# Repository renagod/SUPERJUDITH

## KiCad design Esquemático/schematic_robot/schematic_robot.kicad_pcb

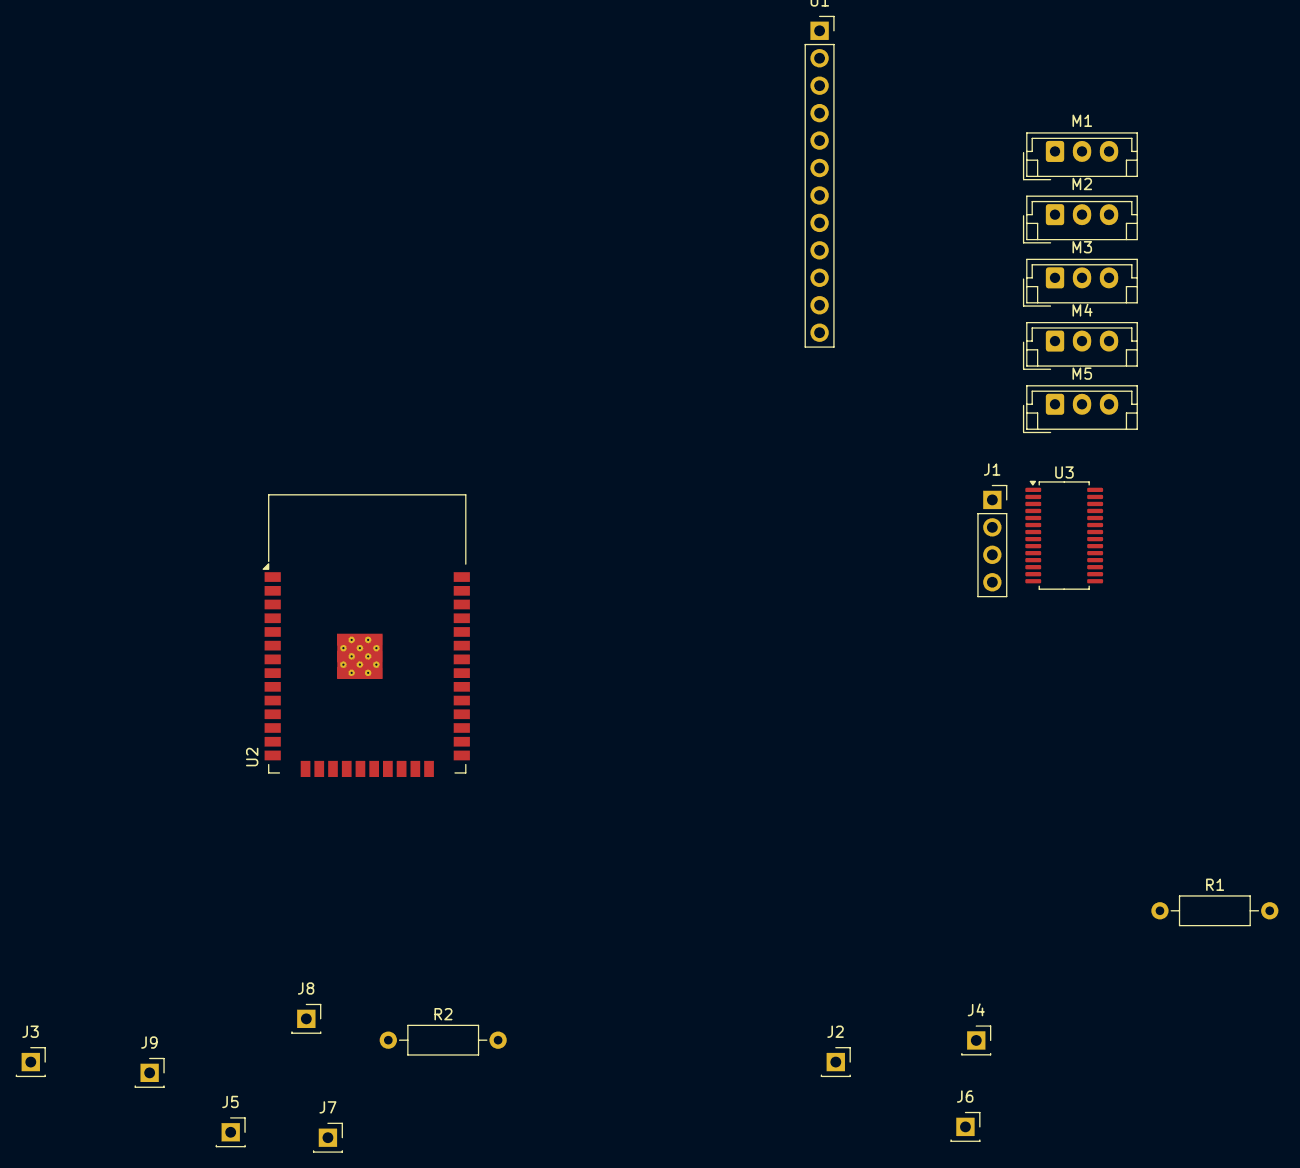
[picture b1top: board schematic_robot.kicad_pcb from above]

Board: 2 copper layers, 19 parts (0 on the bottom side), 18 nets, no tracks yet.

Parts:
J1: Conn_01x04_Pin; PinSocket_1x04_P2.54mm_Vertical
J2, J3, J4, J5, J6, J7, J8, J9: Conn_01x01_Socket; PinSocket_1x01_P2.54mm_Vertical
M1, M2, M3, M4, M5: Motor_Servo; JST_EH_B3B-EH-A_1x03_P2.50mm_Vertical
R1, R2: 4.7k; R_Axial_DIN0207_L6.3mm_D2.5mm_P10.16mm_Horizontal
U1: TB6600; PinSocket_1x12_P2.54mm_Vertical
U2: ESP32-WROOM-32
U3: PCA9685PW; TSSOP-28_4.4x9.7mm_P0.65mm

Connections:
5V: J3.1, J8.1, M1.2 (+), M2.2 (+), M3.2 (+), M4.2 (+), M5.2 (+), R1.1, R2.1, U2.2 (VDD), U3.14 (VSS)
12V: J2.1, J6.1, U1.12 (VCC)
DIR+: U1.4 (DIR+), U2.11 (IO26)
ENA+: U1.2 (ENA+), U2.13 (IO14)
Earth: J5.1, J7.1, U1.1 (ENA-), U1.3 (DIR-), U1.5 (PUL-), U1.11 (GND)
GND: J4.1, J9.1, M1.3 (-), M2.3 (-), M3.3 (-), M4.3 (-), M5.3 (-), U2.1 (GND), U2.15 (GND), U2.38 (GND), U2.39 (GND), U3.25 (EXTCLK), U3.28 (VDD)
unnamed: J1.1, U1.8 (B+)
unnamed: J1.2, U1.7 (B-)
unnamed: J1.3, U1.9 (A-)
unnamed: J1.4, U1.10 (A+)
PUL+: U1.6 (PUL+), U2.10 (IO25)
PWM1: M1.1 (PWM), U3.6 (LED0)
PWM2: M2.1 (PWM), U3.7 (LED1)
PWM3: M3.1 (PWM), U3.8 (LED2)
PWM4: M4.1 (PWM), U3.9 (LED3)
PWM5: M5.1 (PWM), U3.10 (LED4)
SCL: R2.2, U2.36 (IO22), U3.26 (SCL)
SDA: R1.2, U2.33 (IO21), U3.27 (SDA)

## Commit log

2024-04-10 datasheet mg996R
    datasheet
2024-06-23 Kicad Project - Stephan
2024-06-23 teste
2024-06-23 Pasta para projeto de esquemáticos
2024-06-23 gitignore
2024-06-24 marquei coisas sem conexão
    coloquei xzinho
2024-06-24 mudei
    mudei
2024-06-24 datasheet + kicad
    datasheet + kicad
2024-06-24 esquematico
    mudei uns trem
2024-06-24 atualizei uns trem
    esquema
2024-06-24 MUDEI MAIS
    AOBA
2024-06-24 canseira
    eu ein
2024-07-16 Upload da luva
2024-07-18 Esquemático com fonte e substituição de mcu
2024-07-25 Protótipo do código no ESP32
2024-07-25 READme
2024-08-09 Correção final
2024-09-28 Atualização do esquemático e datasheets, exclusão da pasta src
2024-09-28 Exlusão do código antigo
